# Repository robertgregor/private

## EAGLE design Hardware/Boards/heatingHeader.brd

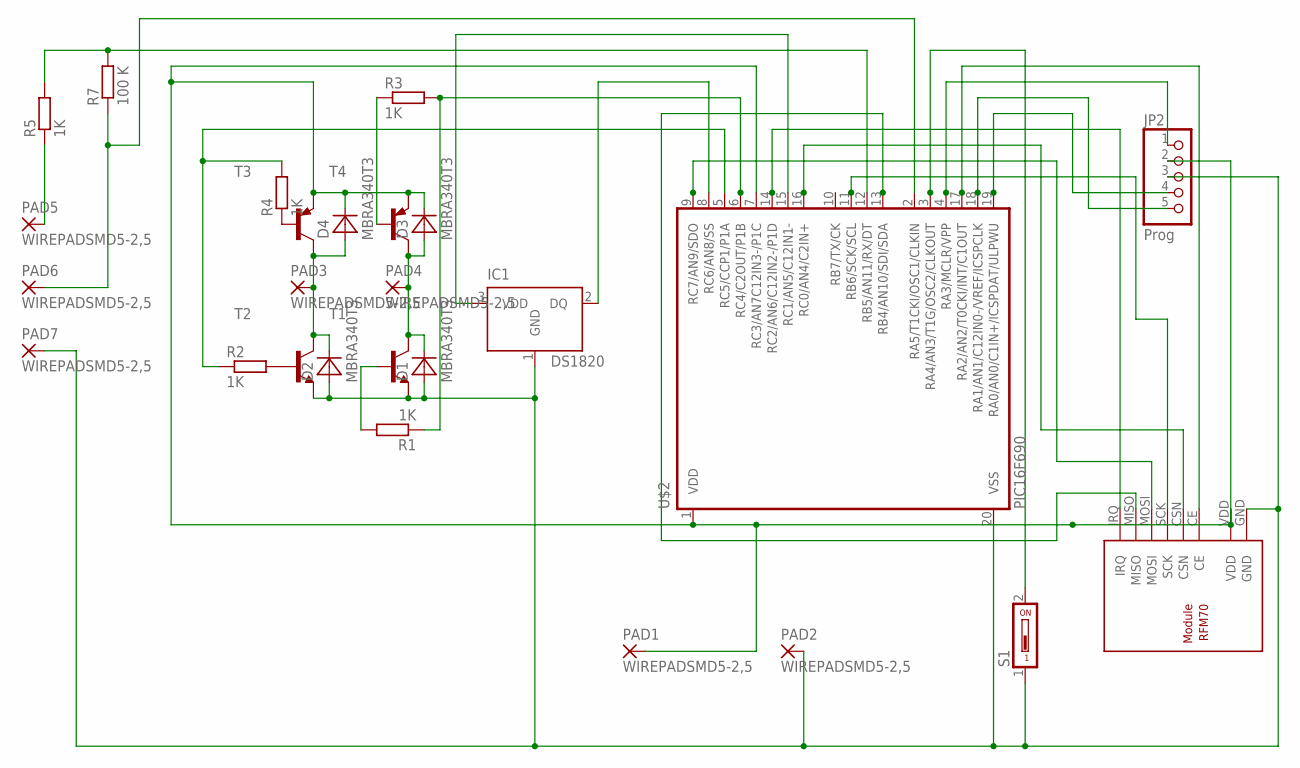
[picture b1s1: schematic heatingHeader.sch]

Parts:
D1, D2, D3, D4: MBRA340T3; SMA
IC1: DS1820; TO-92
JP2: Prog; 1X05
PAD1, PAD2, PAD3, PAD4, PAD5, PAD6, PAD7: WIREPADSMD5-2,5; 5-2,5
R1, R2, R3, R4, R5: 1K; R1206
R7: 100 K; R1206
S1: SD4-01
T1, T2: BC817-40-NPN-SOT23-BEC; SOT23-BEC
T3, T4: BC807-16-PNP-SOT23-BEC; SOT23-BEC
U$1: RFM70
U$2: PIC16F690; SSOP20

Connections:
unnamed: IC1.2 (DQ), U$2.8 (RC6/AN8/SS)
unnamed: D3.C, D4.C, JP2.2, PAD1.1, T3.E, T4.E, U$1.VDD, U$2.1 (VDD), U$2.7 (RC3/AN7C12IN3-/P1C)
unnamed: IC1.3 (VDD), U$2.15 (RC1/AN5/C12IN1-)
unnamed: PAD5.1, R5.1
unnamed: D1.A, D2.A, IC1.1 (GND), JP2.3, PAD2.1, PAD7.1, S1.1, T1.E, T2.E, U$1.GND, U$2.20 (VSS)
unnamed: U$1.MISO, U$2.13 (RB4/AN10/SDI/SDA)
unnamed: D2.C, D4.A, PAD3.1, T2.C, T3.C
unnamed: D1.C, D3.A, PAD4.1, T1.C, T4.C
unnamed: PAD6.1, R7.1, U$2.2 (RA5/T1CKI/OSC1/CLKIN)
unnamed: S1.2, U$2.3 (RA4/AN3/T1G/OSC2/CLKOUT)
unnamed: R2.2, T2.B
unnamed: R4.1, T3.B
unnamed: U$1.CE, U$2.17 (RA2/AN2/T0CKI/INT/C1OUT)
unnamed: JP2.4, U$2.19 (RA0/AN0/C1IN+/ICSPDAT/ULPWU)
unnamed: JP2.5, U$2.18 (RA1/AN1/C12IN0-/VREF/ICSPCLK)
unnamed: U$1.CSN, U$2.16 (RC0/AN4/C2IN+)
unnamed: U$1.IRQ, U$2.14 (RC2/AN6/C12IN2-/P1D)
unnamed: U$1.SCK, U$2.11 (RB6/SCK/SCL)
unnamed: U$1.MOSI, U$2.9 (RC7/AN9/SDO)
unnamed: R1.2, T1.B
unnamed: JP2.1, U$2.4 (RA3/MCLR/VPP)
unnamed: R3.1, T4.B
unnamed: R5.2, R7.2, U$2.12 (RB5/AN11/RX/DT)
unnamed: R1.1, R3.2, U$2.6 (RC4/C2OUT/P1B)
unnamed: R2.1, R4.2, U$2.5 (RC5/CCP1/P1A)

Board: 2 copper layers, 26 parts (9 on the bottom side), 25 nets, no tracks yet.

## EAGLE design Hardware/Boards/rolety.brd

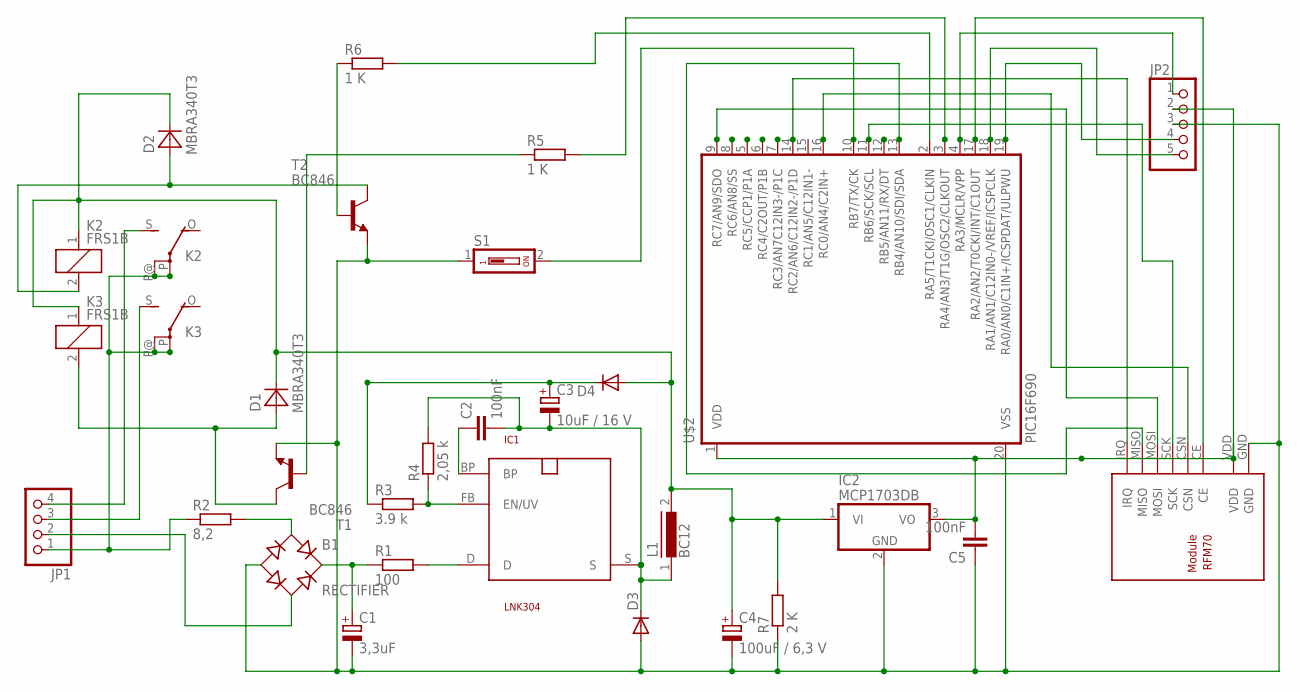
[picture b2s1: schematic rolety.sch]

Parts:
B1: RECTIFIER; TO-269AA
C1: 3,3uF; E5-13
C2, C5: 100nF; C2012
C3: 10uF / 16 V; E2,5-5
C4: 100uF / 6,3 V; E2,5-5
D1, D2: MBRA340T3; SMA
D3, D4: DIODE-DO214AA; DO214AA
IC1: LNK304; SO-8C
IC2: MCP1703DB; SOT223
JP1: PINHD-1X4; 1X04
JP2: PINHD-1X5; 1X05
K2, K3: FRS1B
L1: BC12
R1: 100; R2512W
R2: 8,2; R2512W
R3: 3.9 k; M2012
R4: 2,05 k; M2012
R5, R6: 1 K; M2012
R7: 2 K; M2012
S1: SD4-01
T1, T2: BC846; SOT23
U$1: RFM70
U$2: PIC16F690; SSOP20

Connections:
unnamed: IC1.D, R1.2
unnamed: B1.+, C1.+, R1.1
unnamed: B1.AC1, R2.2
unnamed: B1.AC2, JP1.2
unnamed: B1.-, C1.-, C4.-, C5.1, D3.A, IC2.2 (GND), JP2.3, R7.1, S1.1, T1.2 (E), T2.2 (E), U$1.GND, U$2.20 (VSS)
unnamed: JP1.3, K3.S
unnamed: JP1.4, K2.S
unnamed: C3.+, D4.C, R3.1
unnamed: C2.1, IC1.BP
unnamed: IC1.FB (EN/UV), R3.2, R4.1
unnamed: U$1.MISO, U$2.13 (RB4/AN10/SDI/SDA)
unnamed: C2.2, C3.-, D3.C, IC1.S, L1.1, R4.2
unnamed: D1.A, K3.2, T1.3 (C)
unnamed: R5.1, T1.1 (B)
unnamed: U$1.CE, U$2.17 (RA2/AN2/T0CKI/INT/C1OUT)
unnamed: C5.2, IC2.3 (VO), JP2.2, U$1.VDD, U$2.1 (VDD)
unnamed: JP2.4, U$2.19 (RA0/AN0/C1IN+/ICSPDAT/ULPWU)
unnamed: JP2.5, U$2.18 (RA1/AN1/C12IN0-/VREF/ICSPCLK)
unnamed: U$1.CSN, U$2.16 (RC0/AN4/C2IN+)
unnamed: U$1.IRQ, U$2.14 (RC2/AN6/C12IN2-/P1D)
unnamed: U$1.SCK, U$2.11 (RB6/SCK/SCL)
unnamed: U$1.MOSI, U$2.9 (RC7/AN9/SDO)
unnamed: JP2.1, U$2.4 (RA3/MCLR/VPP)
unnamed: C4.+, D1.C, D2.C, D4.A, IC2.1 (VI), K2.1, K3.1, L1.2, R7.2
unnamed: D2.A, K2.2, T2.3 (C)
unnamed: S1.2, U$2.10 (RB7/TX/CK)
unnamed: R5.2, U$2.3 (RA4/AN3/T1G/OSC2/CLKOUT)
unnamed: JP1.1, K2.P, K2.P@, K3.P, K3.P@, R2.1
unnamed: R6.1, T2.1 (B)
unnamed: R6.2, U$2.2 (RA5/T1CKI/OSC1/CLKIN)

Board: 2 copper layers, 29 parts (14 on the bottom side), 30 nets, no tracks yet.
